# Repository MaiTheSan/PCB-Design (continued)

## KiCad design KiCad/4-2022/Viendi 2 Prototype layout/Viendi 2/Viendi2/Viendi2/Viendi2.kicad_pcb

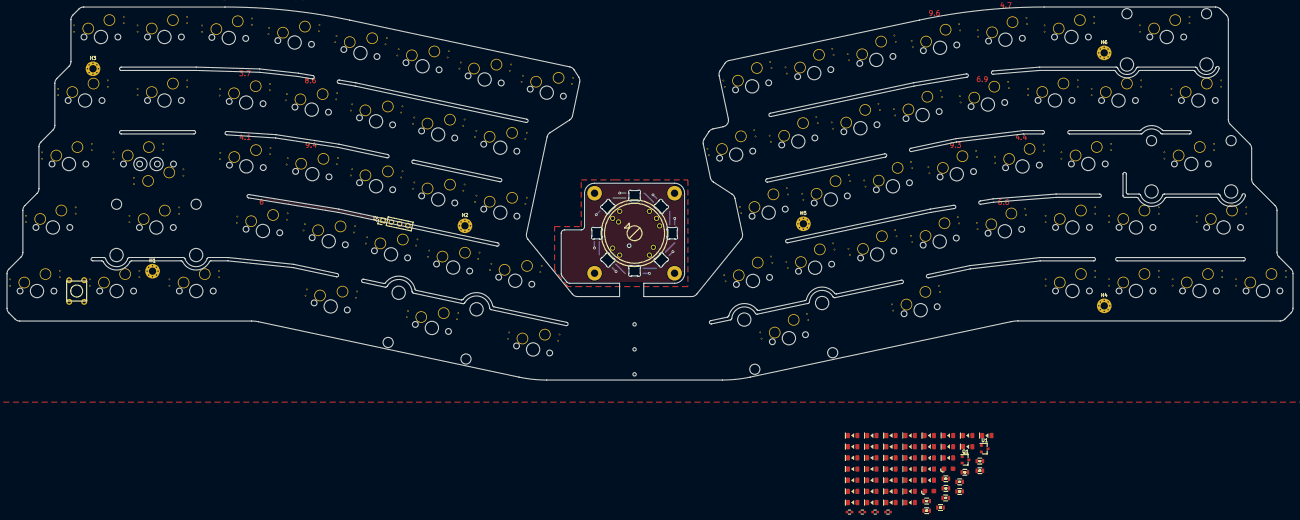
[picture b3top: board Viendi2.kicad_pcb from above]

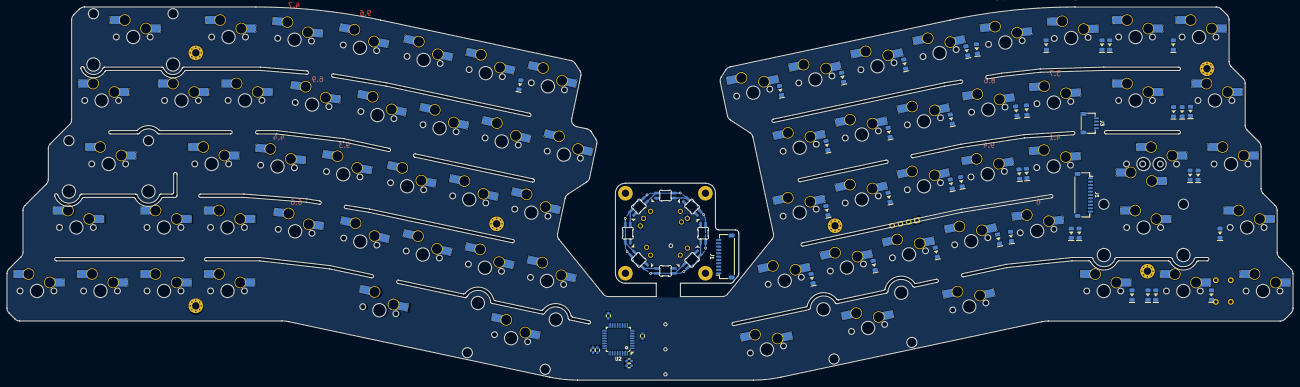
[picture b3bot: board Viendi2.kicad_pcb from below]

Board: 2 copper layers, 385.8 x 111.9 mm, 199 parts (48 on the bottom side), 116 nets.

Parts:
C1, C6: 4.7uF; C_0603
C2, C3, C4, C5, C11: 0.1uF; C_0603
C7, C8: 1uF; CP_EIA-3216
C9, C10: 1uF; C_0603
C12: 10uF (±5%); C_0603
D1, D2, D4, D6, D33, D34, D35, D36, D37, D38, D39, D40, D41, D42, D43, D44, D45, D46, D47, D48, D49, D50, D51, D52, D54, D55, D56, D57, D58, D59, D60, D61, D62, D63, D64, D65, D66, D67, D68, D69, D70, D71, D72, D74, D75, D76, D77, D78, D79, D80, D81, D82, D83, D84, D85, D86, D87, D88, D89, D90, D91, D92, D93, D94, D95, D96, D97, D98, D99, D100, D101, D102, D103, D104, D105, D106, D107: 1N4148W; DIODE_1206_SawnsProjects
H1, H2, H3, H4: MountingHole; MountingHole_2.2mm_M2_Pad
H1#2, H2#2, H3#2, H4#2, H5, H6: MountingHole; MountingHole_2.2mm_M2_Pad_Via
J1, J1#2: Conn_01x11_Female; JST_SH_SM11B-SRSS-TB_1x11-1MP_P1.00mm_Horizontal
J2: Conn_01x04; PinHeader_1x04_P2.54mm_Vertical
J3: Conn_01x04_Female; JST-SR-4
MX1, MX2, MX3, MX4, MX5, MX6, MX7, MX8, MX9, MX10, MX11, MX12, MX13, MX14, MX17, MX19, MX20, MX21, MX22, MX23, MX24, MX25, MX26, MX27, MX28, MX29, MX30, MX33, MX35, MX36, MX37, MX38, MX39, MX40, MX41, MX42, MX43, MX44, MX45, MX49, MX51, MX52, MX53, MX54, MX55, MX56, MX57, MX58, MX59, MX60, MX61, MX62, MX65, MX67, MX68, MX70, MX73, MX74, MX75, MX76: 1U; MXOnly-1U-Hotswap-Sawns
MX15: 2U; MXOnly-2U-Hotswap-Sawns
MX18, MX31, MX66, MX72: 1.5U; MXOnly-1.5U-Hotswap-Sawns
MX34: 1.75U; MXOnly-1.75U-Hotswap-Sawns
MX46, MX50: 2.25U; MXOnly-2.25U-Hotswap-Sawns
MX64: 2.25U; MXOnly-2.25U-Hotswap-ReversedStabilizers-Sawns
MX71: 2.75U; MXOnly-2.75U-Hotswap-ReversedStabilizers-Sawns
MX78: 1.25U; MXOnly-1.25U-Hotswap-Sawns
MX79: 1U; MXOnly-1.75U-Hotswap-Sawns
Q1: DTC123JKAT146; SOT-23
R1: 330R; R_0805
R2, R3: 22R; R_0805
R4: 1.5k; R_0805
R5, R6: 100k; R_0805
R7, R8: 10k; R_0805
R9: 100R; R_0805
R10: 330k (±1%); R_0805
R11: 1M (±1%); R_0805
RGB1, RGB2, RGB3, RGB4, RGB5, RGB6, RGB7, RGB8: WS2812B; MX_SK6812MINI-E_MID_Viendi2
SW1: StickSW+KNOB; RKJXT1F_4DirectionStickSW_RotaryEncoder
SW1#2: SW_Push; PushButton_6x6mm_TH_Pretty
U1: MCP1700-5002E_SOT23; SOT-23
U2: STM32F072CBTx; LQFP-48_7x7mm_P0.5mm

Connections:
+3V3: C1.1, C2.1, C3.1, C4.1, C5.1, C6.1, C8.1, J2.4, R4.1, R6.1, R7.2, R8.1, SW1#2.1, U1.2, U2.1, U2.9, U2.24, U2.36, U2.48
+5V: C7.1, J1#2.1, R5.2, U1.3
ABC1: U2.4, U2.10
ABC2: U2.3, U2.11
ABC3: U2.2, U2.12
B: D35.1, D69.1, D71.1, D74.1, D76.1, D78.1, D80.1, D82.1, D84.1, D86.1, D88.1, D90.1, D92.1, D94.1, D96.1
Boot0: C12.1, R10.1, R11.1
C: D33.1, D38.1, D39.1, D40.1, D41.1, D42.1, D43.1, D44.1, D45.1, D46.1, D47.1, D48.1, D49.1, D50.1, D51.1, D52.1, U2.16
Col0: MX1.1, MX17.1, MX33.1, MX49.1, MX65.1, U2.13
Col1: MX2.1, MX18.1, MX34.2, MX50.1, MX66.1, MX78.1, U2.14
Col3: MX3.1, MX19.1, MX35.1, MX51.1, U2.22
Col4: MX4.1, MX20.1, MX36.1, MX52.1, MX68.1, U2.21
Col5: MX5.1, MX21.1, MX37.1, MX53.1, MX64.1, U2.20
Col6: MX6.1, MX22.1, MX38.1, MX54.1, U2.19
Col7: MX7.1, MX23.1, MX39.1, MX55.1, MX70.1, U2.18
Col8: MX8.1, U2.17
Col9: MX9.1, MX24.1, MX40.1, MX56.1, MX71.1, U2.39
Col10: MX10.1, MX25.1, MX41.1, MX57.1, MX72.1, U2.46
Col11: MX11.1, MX26.1, MX42.1, MX58.1, MX73.1, U2.45
Col12: MX12.1, MX27.1, MX43.1, MX59.1, MX74.1, U2.38
Col13: MX13.1, MX28.1, MX44.1, MX60.1, MX75.1, U2.43
Col14: MX14.1, MX29.1, MX45.1, MX61.1, MX76.1, U2.42
Col15: MX15.1, MX30.1, MX46.1, MX62.1, U2.41
Col16: MX31.1, MX79.1, U2.40
Com: D34.1, D54.1, D55.1, D56.1, D57.1, D58.1, D59.1, D60.1, D61.1, D62.1, D63.1, D64.1, D65.1, D66.1, D67.1, D68.1, U2.15
D: D37.1, D70.1, D72.1, D75.1, D77.1, D79.1, D81.1, D83.1, D85.1, D87.1, D89.1, D91.1, D93.1, D95.1, D97.1, D98.1
E_A: C10.1, J1#2.10, R8.2, U2.30
E_B: C9.2, J1#2.4, R7.1, U2.28
GND: C1.2, C2.2, C3.2, C4.2, C5.2, C6.2, C7.2, C8.2, C9.1, C10.2, C11.1, C12.2, J1#2.11, J2.1, Q1.2, R5.1, R6.2, R11.2, U1.1, U2.8, U2.23, U2.35, U2.47
NRST: C11.2, R9.1, U2.7
unnamed: D1.1, R10.2
unnamed: D1.2, Q1.1, SW1#2.2
unnamed: D2.2, MX65.2
unnamed: D4.2, MX66.2
unnamed: D6.2, MX67.2
unnamed: D33.2, J1#2.2
unnamed: D34.2, J1#2.3
unnamed: D35.2, J1#2.5
unnamed: D36.2, J1#2.8
unnamed: D37.2, J1#2.9
unnamed: D38.2, MX1.2
unnamed: D39.2, MX2.2
unnamed: D40.2, MX3.2
unnamed: D41.2, MX4.2
unnamed: D42.2, MX5.2
unnamed: D43.2, MX6.2
unnamed: D44.2, MX7.2
unnamed: D45.2, MX8.2
unnamed: D46.2, MX9.2
unnamed: D47.2, MX10.2
unnamed: D48.2, MX11.2
unnamed: D49.2, MX12.2
unnamed: D50.2, MX13.2
unnamed: D51.2, MX14.2
unnamed: D52.2, MX15.2
unnamed: D54.2, MX17.2
unnamed: D55.2, MX18.2
unnamed: D56.2, MX19.2
unnamed: D57.2, MX20.2
unnamed: D58.2, MX21.2
unnamed: D59.2, MX22.2
unnamed: D60.2, MX23.2
unnamed: D61.2, MX24.2
unnamed: D62.2, MX25.2
unnamed: D63.2, MX26.2
unnamed: D64.2, MX27.2
unnamed: D65.2, MX28.2
unnamed: D66.2, MX29.2
unnamed: D67.2, MX30.2
unnamed: D68.2, MX31.2
unnamed: D69.2, MX33.2
unnamed: D70.2, MX49.2
unnamed: D71.2, MX34.1, MX78.2
unnamed: D72.2, MX50.2
unnamed: D74.2, MX35.2
unnamed: D75.2, MX51.2
unnamed: D76.2, MX36.2
unnamed: D77.2, MX52.2
unnamed: D78.2, MX37.2
unnamed: D79.2, MX53.2
unnamed: D80.2, MX38.2
unnamed: D81.2, MX54.2
unnamed: D82.2, MX39.2
unnamed: D83.2, MX55.2
unnamed: D84.2, MX40.2
unnamed: D85.2, MX56.2
unnamed: D86.2, MX41.2
unnamed: D87.2, MX57.2
unnamed: D88.2, MX42.2
unnamed: D89.2, MX58.2
unnamed: D90.2, MX43.2
unnamed: D91.2, MX59.2
unnamed: D92.2, MX44.2
unnamed: D93.2, MX60.2
unnamed: D94.2, MX45.2
unnamed: D95.2, MX61.2
unnamed: D96.2, MX46.2
unnamed: D97.2, MX62.2
unnamed: D98.2, MX79.2
unnamed: D99.2, MX68.2
unnamed: D100.2, MX64.2
unnamed: D101.2, MX70.2
unnamed: D102.2, MX71.2
unnamed: D103.2, MX72.2
unnamed: D104.2, MX73.2
unnamed: D105.2, MX74.2
unnamed: D106.2, MX75.2
unnamed: D107.2, MX76.2
unnamed: J1#2.6, R1.1
unnamed: Q1.3, R9.2
unnamed: R2.2, U2.32
unnamed: R3.2, R4.2, U2.33
Push: J1#2.7, U2.29
RGB_IN: R1.2, U2.31
SWCLK: J2.3, U2.37
SWDIO: J2.2, U2.34

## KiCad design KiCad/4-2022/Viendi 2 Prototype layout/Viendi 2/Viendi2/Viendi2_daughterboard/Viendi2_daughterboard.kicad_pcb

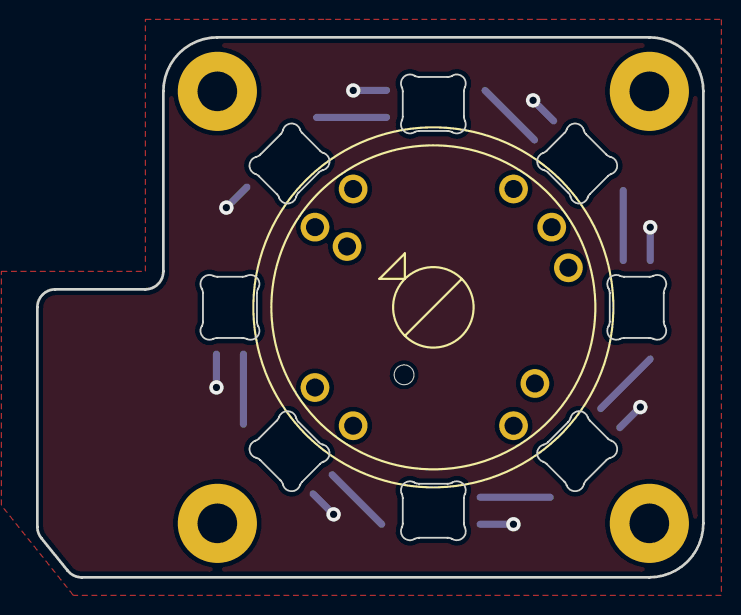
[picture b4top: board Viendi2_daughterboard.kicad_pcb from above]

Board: 2 copper layers, 37.0 x 30.0 mm, 14 parts (1 on the bottom side), 9 nets.

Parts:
H1, H2, H3, H4: MountingHole; MountingHole_2.2mm_M2_Pad
J1: Conn_01x11_Female; JST_SH_SM11B-SRSS-TB_1x11-1MP_P1.00mm_Horizontal
RGB1, RGB2, RGB3, RGB4, RGB5, RGB6, RGB7, RGB8: WS2812B; MX_SK6812MINI-E_MID_Viendi2
SW1: StickSW+KNOB; RKJXT1F_4DirectionStickSW_RotaryEncoder

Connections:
+5V: RGB1.1, RGB2.1, RGB3.1, RGB4.1, RGB5.1, RGB6.1, RGB7.1, RGB8.1
GND: RGB1.3, RGB2.3, RGB3.3, RGB4.3, RGB5.3, RGB6.3, RGB7.3, RGB8.3, SW1.7, SW1.10
unnamed: RGB1.2, RGB2.4
unnamed: RGB2.2, RGB3.4
unnamed: RGB3.2, RGB4.4
unnamed: RGB4.2, RGB5.4
unnamed: RGB5.2, RGB6.4
unnamed: RGB6.2, RGB7.4
unnamed: RGB7.2, RGB8.4

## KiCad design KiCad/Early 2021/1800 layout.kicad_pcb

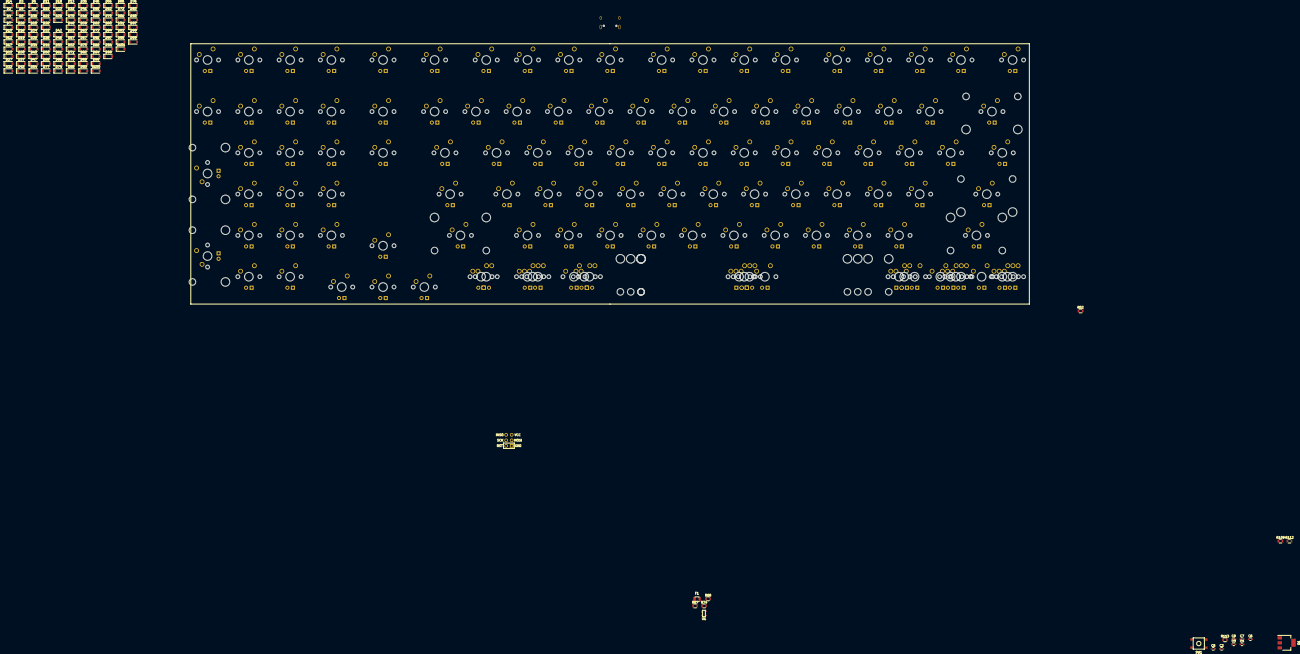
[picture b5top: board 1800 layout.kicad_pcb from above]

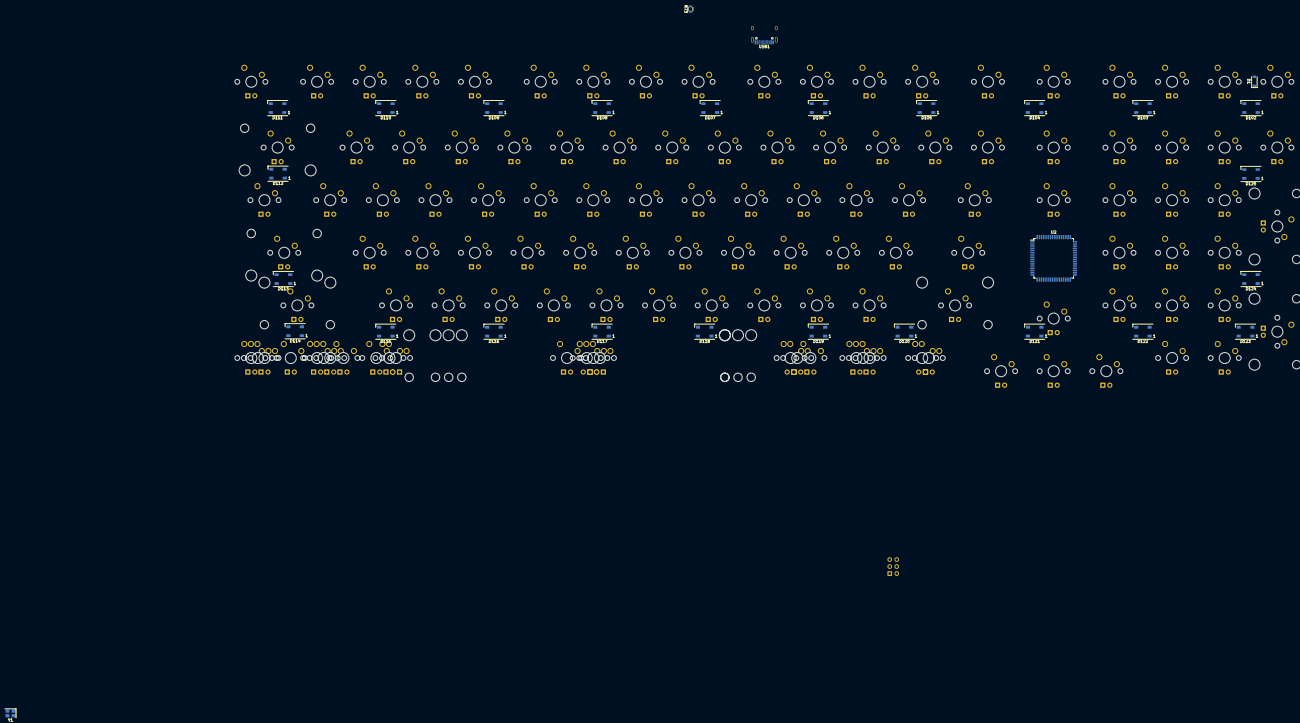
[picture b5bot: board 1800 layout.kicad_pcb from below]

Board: 2 copper layers, 266 parts (29 on the bottom side), 143 nets, no tracks yet.

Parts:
C2, C5: 1uF; C_0603
C3, C4: 22pF; C_0603
C6, C7, C8: 0.1uF; C_0603
D1, D2, D3, D4, D5, D6, D7, D8, D9, D10, D11, D12, D13, D14, D15, D16, D17, D18, D19, D20, D21, D22, D23, D24, D25, D26, D27, D28, D29, D30, D31, D32, D33, D34, D35, D36, D37, D38, D39, D40, D41, D42, D43, D44, D45, D46, D47, D48, D49, D50, D51, D52, D53, D54, D55, D56, D57, D58, D59, D60, D61, D62, D63, D64, D65, D66, D67, D68, D69, D70, D71, D72, D73, D74, D75, D76, D77, D78, D79, D80, D81, D82, D83, D84, D85, D86, D87, D88, D89, D90, D91, D92, D93, D94, D95, D96, D97, D98, D99, D100, D101: SOD_123; D_SOD-123-Pretty
D102, D103, D104, D105, D106, D107, D108, D109, D110, D111, D112, D113, D114, D115, D116, D117, D118, D119, D120, D121, D122, D123, D124, D125: WS2812B; LED_WS2812B_PLCC4_5.0x5.0mm_P3.2mm
F1: 500mA; Fuse_SMD1206_Reflow
J1: AVR-ISP-6; Reset_Pretty-Mask
MX_0, MX_1, MX_2, MX_3, MX_4, MX_5, MX_6, MX_7, MX_8, MX_9: 1U; MXOnly-1U
MX_'1: 1U; MXOnly-1U
MX_+1: 1U; MXOnly-1U
MX_-1: 1U; MXOnly-1U
MX_/?/2: 1U; MXOnly-1U
MX_;1: 1U; MXOnly-1U
MX_<2: 1U; MXOnly-1U
MX_>2: 1U; MXOnly-1U
MX_A1: 1U; MXOnly-1U
MX_ALT1: 1,5U FLIPPED; MXOnly-1.5U-FLIPPED
MX_ALT2, MX_ALT3: 1,25U; MXOnly-1.25U
MX_BkSp1: 2U; MXOnly-2U
MX_CapLk1: 1,75U; MXOnly-1.75U
MX_D1: 1U; MXOnly-1U
MX_Delete1: 1U; MXOnly-1U
MX_Down1: 1U; MXOnly-1U
MX_E1: 1U; MXOnly-1U
MX_ENTER1: 2,25U; MXOnly-2.25U
MX_ESC1: 1U; MXOnly-1U
MX_F1, MX_F2, MX_F3, MX_F4, MX_F5, MX_F6, MX_F7, MX_F8, MX_F9, MX_F10, MX_F11, MX_F12, MX_F13, MX_F14: 1U; MXOnly-1U
MX_FN1, MX_FN2, MX_FN3, MX_FN4: 1U; MXOnly-1U
MX_G1: 1U; MXOnly-1U
MX_H1: 1U; MXOnly-1U
MX_I1: 1U; MXOnly-1U
MX_J1: 1U; MXOnly-1U
MX_K1: 1U; MXOnly-1U
MX_L1: 1U; MXOnly-1U
MX_LControl1: 1,5U; MXOnly-1.5U-FLIPPED
MX_LControl2: 1,25; MXOnly-1.25U
MX_LShift1: 2,25U FLIPPED; MXOnly-2.25U-ReversedStabilizers
MX_LWin1, MX_LWin3: 1U; MXOnly-1U
MX_LWin2: 1,25U NoLed; MXOnly-1.25U-NoLED
MX_Left1: 1U; MXOnly-1U
MX_O1: 1U; MXOnly-1U
MX_P1: 1U; MXOnly-1U
MX_PrtSc1: 1U; MXOnly-1U
MX_Q1: 1U; MXOnly-1U
MX_R1: 1U; MXOnly-1U
MX_RAlt1, MX_RAlt3: 1,25U; MXOnly-1.25U
MX_RAlt2: 1,5U FLIPPED; MXOnly-1.5U-FLIPPED
MX_RAlt4: 1,5U; MXOnly-1.5U
MX_RControl1: 1,25U NoLed; MXOnly-1.25U-NoLED
MX_RControl2: 1U; MXOnly-1U
MX_RControl3: 1,5U; MXOnly-1.5U
MX_RShift2: 2,75U FLIPPED; MXOnly-2.75U-ReversedStabilizers
MX_RWin1: NoLed; MXOnly-1.25U-NoLED
MX_RWin2: 1,5U; MXOnly-1.5U
MX_RWin3, MX_RWin4: 1U; MXOnly-1U
MX_Right1: 1U; MXOnly-1U
MX_S1: 1U; MXOnly-1U
MX_SpaceBar1, MX_SpaceBar2: 6,25U FLIPPED; MXOnly-6.25U-FLIPPED-ReversedStabilizers
MX_SpaceBar3, MX_SpaceBar4: 7U; MXOnly-7U-ReversedStabilizers
MX_T1: 1U; MXOnly-1U
MX_U1: 1U; MXOnly-1U
MX_W1: 1U; MXOnly-1U
MX_Y1: 1U; MXOnly-1U
MX_[1: 1U; MXOnly-1U
MX_]1: 1U; MXOnly-1U
MX_`~1: 1U; MXOnly-1U
MX_b1: 1U; MXOnly-1U
MX_c1: 1U; MXOnly-1U
MX_insert1: 1U; MXOnly-1U
MX_m2: 1U; MXOnly-1U
MX_n2: 1U; MXOnly-1U
MX_num0, MX_num1, MX_num2, MX_num3, MX_num4, MX_num5, MX_num6, MX_num7, MX_num8, MX_num9: 1U; MXOnly-1U
MX_num*1: 1U; MXOnly-1U
MX_num+1: 2U; MXOnly-2U
MX_num-1: 1U; MXOnly-1U
MX_num/1: 1U; MXOnly-1U
MX_numDel1: 1U; MXOnly-1U
MX_numEnter1: 2U; MXOnly-2U
MX_numLk1: 1U; MXOnly-1U
MX_tab1: 1,5U; MXOnly-1.5U
MX_up1: 1U; MXOnly-1U
MX_v1: 1U; MXOnly-1U
MX_x1: 1U; MXOnly-1U
MX_z1: 1U; MXOnly-1U
MX_|\1: 1.5U; MXOnly-1.5U
Q1: DSS60601MZ4-13; SOT-223-3_TabPin2
R52: 500; R_0805
R67, R68: 22; R_0805
R73, R74: 5.1k; R_0805
R109: 1.5k; R_0805
R112: 10k; R_0805
R113: 1k; R_0805
SW1: SW_Push; SKQG-1155865
U1: PRTR5V0U2X; SOT143B
U2: AT90USB1286-AU; TQFP-64_14x14mm_P0.8mm
USB1: HRO-TYPE-C-31-M-12; HRO-TYPE-C-31-M-12-Assembly
Y1: 16MHz; Crystal_SMD_3225-4Pin_3.2x2.5mm

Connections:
+5V: C5.2, C6.2, C7.2, C8.2, F1.1, J1.2, R112.1, U2.3, U2.8, U2.21, U2.52, U2.64
D+: R68.1, U2.5
D-: R67.1, U2.4
GND: C2.2, C3.2, C4.2, C5.1, C6.1, C7.1, C8.1, J1.6, Q1.3, R73.1, R74.1, R113.2, SW1.1, U1.1, U2.6, U2.22, U2.53, U2.63, USB1.1, USB1.12, USB1.13, Y1.2, Y1.4
MISO: J1.1, U2.13
MOSI: J1.4, U2.12
unnamed: C2.1, U2.7
unnamed: D1.2, MX_FN1.2
unnamed: D2.2, MX_num-1.2
unnamed: D3.2, MX_num+1.2
unnamed: D4.2, MX_numEnter1.2
unnamed: D5.2, MX_FN2.2
unnamed: D6.2, MX_num*1.2
unnamed: D7.2, MX_num7.2
unnamed: D8.2, MX_num4.2
unnamed: D9.2, MX_num1.2
unnamed: D10.2, MX_num0.2
unnamed: D11.2, MX_FN3.2
unnamed: D12.2, MX_num/1.2
unnamed: D13.2, MX_num8.2
unnamed: D14.2, MX_num5.2
unnamed: D15.2, MX_num2.2
unnamed: D16.2, MX_numDel1.2
unnamed: D17.2, MX_FN4.2
unnamed: D18.2, MX_numLk1.2
unnamed: D19.2, MX_num9.2
unnamed: D20.2, MX_num6.2
unnamed: D21.2, MX_num3.2
unnamed: D22.2, MX_Right1.2
unnamed: D23.2, MX_PrtSc1.2
unnamed: D24.2, MX_insert1.2
unnamed: D25.2, MX_Delete1.2
unnamed: D26.2, MX_up1.2
unnamed: D27.2, MX_Down1.2
unnamed: D28.2, MX_ESC1.2
unnamed: D29.2, MX_`~1.2
unnamed: D30.2, MX_tab1.2
unnamed: D31.2, MX_CapLk1.2
unnamed: D32.2, MX_LShift1.2
unnamed: D33.2, MX_Left1.2
unnamed: D34.2, MX_F1.2
unnamed: D35.2, MX_1.2
unnamed: D36.2, MX_Q1.2
unnamed: D37.2, MX_A1.2
unnamed: D38.2, MX_z1.2
unnamed: D39.2, MX_LControl1.2
unnamed: D40.2, MX_F2.2
unnamed: D41.2, MX_2.2
unnamed: D42.2, MX_W1.2
unnamed: D43.2, MX_S1.2
unnamed: D44.2, MX_x1.2
unnamed: D45.2, MX_LWin1.2
unnamed: D46.2, MX_F3.2
unnamed: D47.2, MX_3.2
unnamed: D48.2, MX_E1.2
unnamed: D49.2, MX_D1.2
unnamed: D50.2, MX_c1.2
unnamed: D51.2, MX_ALT1.2
unnamed: D52.2, MX_F4.2
unnamed: D53.2, MX_4.2
unnamed: D54.2, MX_R1.2
unnamed: D55.2, MX_F5.2
unnamed: D56.2, MX_v1.2
unnamed: D57.2, MX_5.2
unnamed: D58.2, MX_T1.2
unnamed: D59.2, MX_G1.2
unnamed: D60.2, MX_b1.2
unnamed: D61.2, MX_SpaceBar1.2
unnamed: D62.2, MX_F6.2
unnamed: D63.2, MX_6.2
unnamed: D64.2, MX_Y1.2
unnamed: D65.2, MX_H1.2
unnamed: D66.2, MX_n2.2
unnamed: D67.2, MX_F7.2
unnamed: D68.2, MX_7.2
unnamed: D69.2, MX_U1.2
unnamed: D70.2, MX_J1.2
unnamed: D71.2, MX_m2.2
unnamed: D72.2, MX_F8.2
unnamed: D73.2, MX_8.2
unnamed: D74.2, MX_I1.2
unnamed: D75.2, MX_K1.2
unnamed: D76.2, MX_<2.2
unnamed: D77.2, MX_RAlt1.2
unnamed: D78.2, MX_F9.2
unnamed: D79.2, MX_9.2
unnamed: D80.2, MX_O1.2
unnamed: D81.2, MX_L1.2
unnamed: D82.2, MX_>2.2
unnamed: D83.2, MX_RWin1.2
unnamed: D84.2, MX_F10.2
unnamed: D85.2, MX_0.2
unnamed: D86.2, MX_P1.2
unnamed: D87.2, MX_;1.2
unnamed: D88.2, MX_/?/2.2
unnamed: D89.2, MX_RControl1.2
unnamed: D90.2, MX_F11.2
unnamed: D91.2, MX_-1.2
unnamed: D92.2, MX_[1.2
unnamed: D93.2, MX_'1.2
unnamed: D94.2, MX_F12.2
unnamed: D95.2, MX_+1.2
unnamed: D96.2, MX_]1.2
unnamed: D97.2, MX_F13.2
unnamed: D98.2, MX_F14.2
unnamed: D99.2, MX_BkSp1.2
unnamed: D100.2, MX_ENTER1.2
unnamed: D101.2, MX_RShift2.2
unnamed: D102.1, D103.1, D104.1, D105.1, D106.1, D107.1, D108.1, D109.1, D110.1, D111.1, D112.1, D113.1, D114.1, D115.1, D116.1, D117.1, D118.1, D119.1, D120.1, D121.1, D122.1, D123.1, D124.1, D125.1
unnamed: D102.2, D103.4
unnamed: D102.3, D103.3, D104.3, D105.3, D106.3, D107.3, D108.3, D109.3, D110.3, D111.3, D112.3, D113.3, D114.3, D115.3, D116.3, D117.3, D118.3, D119.3, D120.3, D121.3, D122.3, D123.3, D124.3, D125.3
unnamed: D103.2, D104.4
unnamed: D104.2, D105.4
unnamed: D105.2, D106.4
unnamed: D106.2, D107.4
unnamed: D107.2, D108.4
unnamed: D108.2, D109.4
unnamed: D109.2, D110.4
unnamed: D110.2, D111.4
unnamed: D111.2, D112.4
unnamed: D112.2, D113.4
unnamed: D113.2, D114.4
unnamed: D114.2, D115.4
unnamed: D116.4, D117.2
unnamed: D117.4, D118.2
unnamed: D118.4, D119.2
unnamed: D119.4, D120.2
unnamed: D120.4, D121.2
unnamed: D121.4, D122.2
unnamed: D122.4, D123.2
unnamed: D123.4, D124.2
unnamed: D124.4, D125.2
unnamed: Q1.1, R109.1
unnamed: R67.2, U1.3, USB1.5, USB1.7
unnamed: R68.2, U1.2, USB1.6, USB1.8
unnamed: R73.2, USB1.4
unnamed: R74.2, USB1.10
unnamed: R113.1, U2.43
RESET: J1.5, R112.2, SW1.2, U2.20
SCK: J1.3, U2.11
VCC: F1.2, U1.4, USB1.2, USB1.11
XTAL1: C3.1, U2.24, Y1.1
XTAL2: C4.1, U2.23, Y1.3

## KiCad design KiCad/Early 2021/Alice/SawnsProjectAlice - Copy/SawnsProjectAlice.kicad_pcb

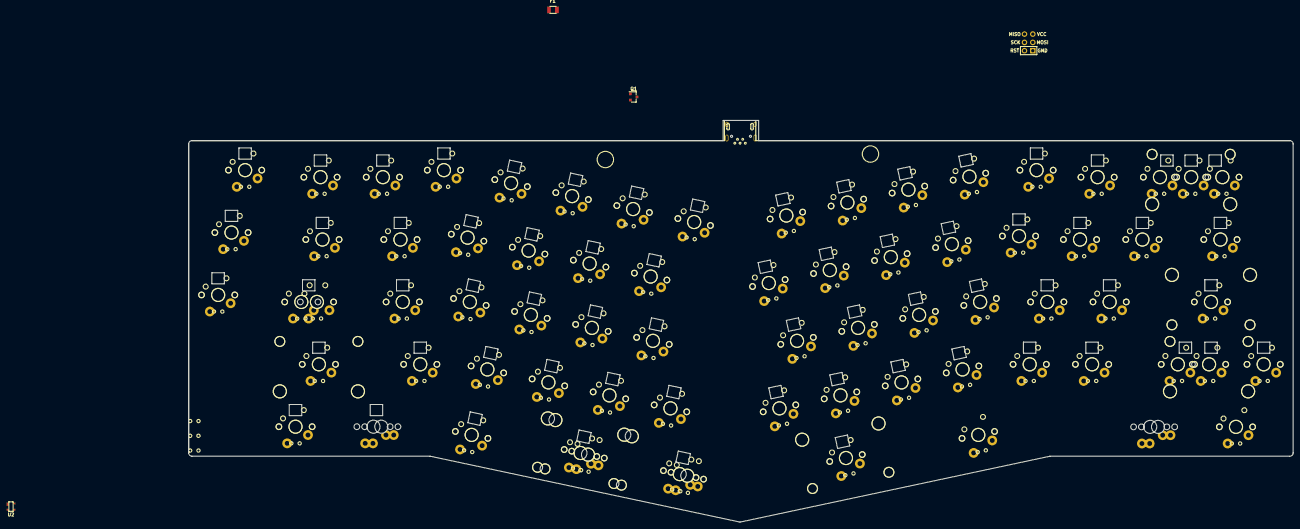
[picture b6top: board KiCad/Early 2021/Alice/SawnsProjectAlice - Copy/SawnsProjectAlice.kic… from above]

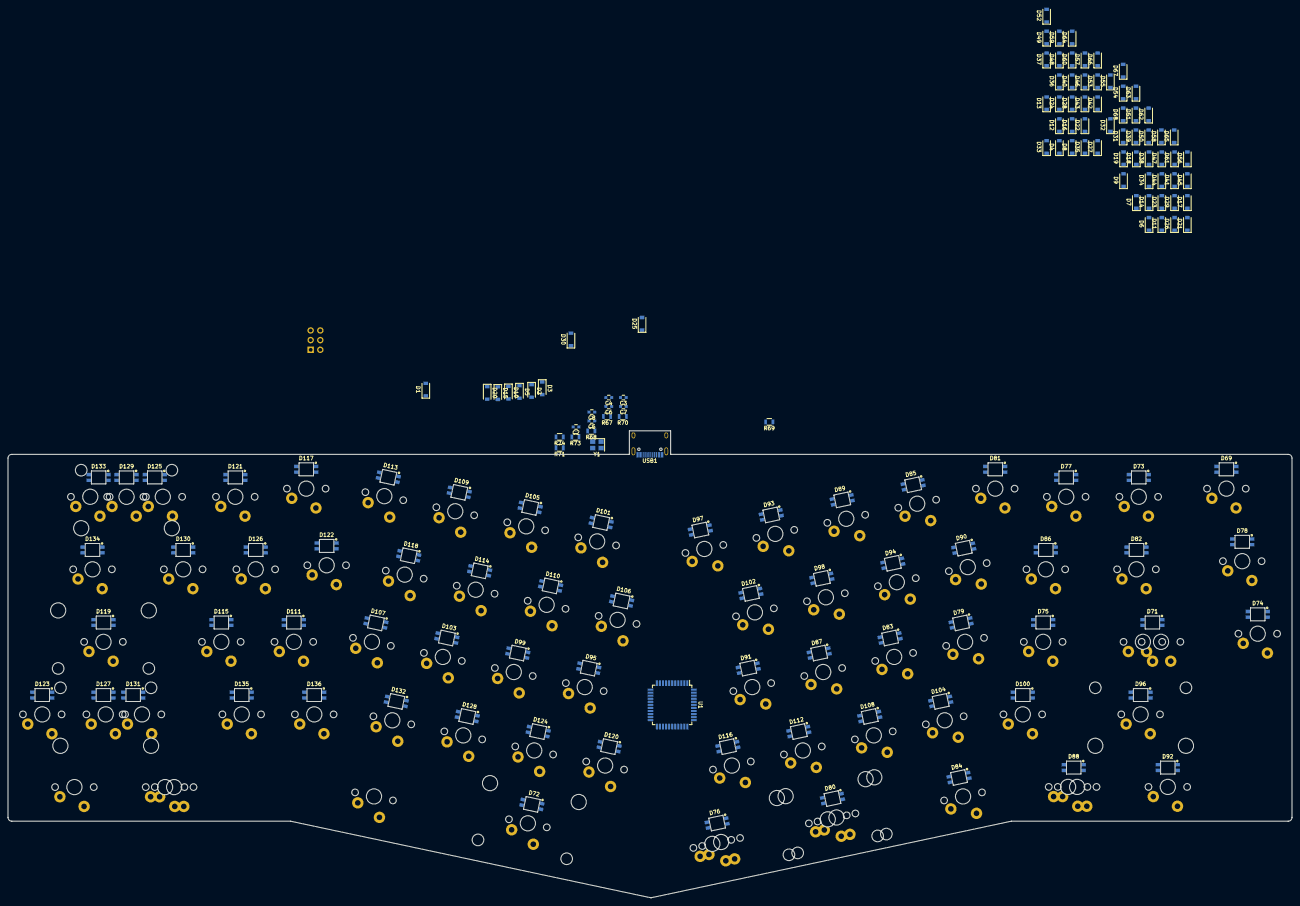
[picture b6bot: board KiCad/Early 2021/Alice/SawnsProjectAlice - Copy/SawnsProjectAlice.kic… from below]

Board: 2 copper layers, 337.2 x 122.6 mm, 231 parts (152 on the bottom side), 171 nets, no tracks yet.

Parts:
C2: 10uF; C_0603
C3, C4, C5: 0.1uF; C_0603
C6: 1uF; C_0603
C7, C8: 22pF; C_0603
D1, D2, D3, D4, D5, D6, D7, D8, D9, D10, D11, D12, D13, D14, D15, D16, D17, D18, D19, D20, D21, D22, D23, D24, D25, D26, D27, D28, D29, D30, D31, D32, D33, D34, D35, D36, D37, D38, D39, D40, D41, D42, D43, D44, D45, D46, D47, D48, D49, D50, D51, D52, D53, D54, D55, D56, D57, D58, D59, D60, D61, D62, D63, D64, D65, D66, D67, D68: SOD_123; D_SOD-123-Pretty
D69, D71, D72, D73, D74, D75, D76, D77, D78, D79, D80, D81, D82, D83, D84, D85, D86, D87, D88, D89, D90, D91, D92, D93, D94, D95, D96, D97, D98, D99, D100, D101, D102, D103, D104, D105, D106, D107, D108, D109, D110, D111, D112, D113, D114, D115, D116, D117, D118, D119, D120, D121, D122, D123, D124, D125, D126, D127, D128, D129, D130, D131, D132, D133, D134, D135, D136: WS2812B; RGB-6028
F1: 500mA; Fuse_SMD1206_Reflow
K_0, K_1, K_2, K_3, K_4, K_5, K_6, K_7, K_8, K_9, K_.1: 1U; MXOnly-1U-NoLED
K_'1: 1U; MXOnly-1U-NoLED
K_+1: 1U; MXOnly-1U-NoLED
K_,1: 1U; MXOnly-1U-NoLED
K_-_1: 1U; MXOnly-1U-NoLED
K_/?/1: 1U; MXOnly-1U-NoLED
K_;1: 1U; MXOnly-1U-NoLED
K_A1: 1U; MXOnly-1U-NoLED
K_Alt1: 1.25U; MXOnly-1.25U-NoLED
K_B1: 1U; MXOnly-1U-NoLED
K_BkSp1: 1U; MXOnly-1U-NoLED
K_BkSp2: 2U; MXOnly-2U-ReversedStabilizers-NoLED
K_C1: 1U; MXOnly-1U-NoLED
K_CapLk1, K_CapLk2: MX-1U-MX_Alps_Hybrids; MXOnly-1U-NoLED
K_D1: 1U; MXOnly-1U-NoLED
K_Delete1: 1U; MXOnly-1U-NoLED
K_E1: 1U; MXOnly-1U-NoLED
K_ESC1: 1U; MXOnly-1U-NoLED
K_Enter1: 2.25U; MXOnly-2.25U-NoLED
K_F1: 1U; MXOnly-1U-NoLED
K_FN1: 1U; MXOnly-1U-NoLED
K_G1: 1U; MXOnly-1U-NoLED
K_H1: 1U; MXOnly-1U-NoLED
K_I1: 1U; MXOnly-1U-NoLED
K_J1: 1U; MXOnly-1U-NoLED
K_K1: 1U; MXOnly-1U-NoLED
K_L1: 1U; MXOnly-1U-NoLED
K_LControl1: 1.5U; MXOnly-1.5U-NoLED
K_LShift1: MX-1U-MX_Alps_Hybrids; MXOnly-2.25U-ReversedStabilizers-NoLED
K_LWin1: 1.25U; MXOnly-1.25U-NoLED
K_LWin2: 1U; MXOnly-1U-NoLED
K_M1: 1U; MXOnly-1U-NoLED
K_N1: 1U; MXOnly-1U-NoLED
K_O1: 1U; MXOnly-1U-NoLED
K_P1: 1U; MXOnly-1U-NoLED
K_PgDn1: 1U; MXOnly-1U-NoLED
K_PgUp1: 1U; MXOnly-1U-NoLED
K_Q1: 1U; MXOnly-1U-NoLED
K_R1: 1U; MXOnly-1U-NoLED
K_RShift1: 1.75U; MXOnly-1.75U-NoLED
K_RShift2: 2.75U; MXOnly-2.75U-ReversedStabilizers-NoLED
K_RWin1: 1U; MXOnly-1U-NoLED
K_RWin2: 1.25U; MXOnly-1.25U-NoLED
K_S1: 1U; MXOnly-1U-NoLED
K_T1: 1U; MXOnly-1U-NoLED
K_Tab1: 1.5U; MXOnly-1.5U-NoLED
K_U1: 1U; MXOnly-1U-NoLED
K_V1: 1U; MXOnly-1U-NoLED
K_W1: 1U; MXOnly-1U-NoLED
K_X1: 1U; MXOnly-1U-NoLED
K_Y1: 1U; MXOnly-1U-NoLED
K_Z1: 1U; MXOnly-1U-NoLED
K_]}1: 1U; MXOnly-1U-NoLED
K_`1: 1U; MXOnly-1U-NoLED
K_xn1: 1U; MXOnly-1U-NoLED
K_{[1: 1U; MXOnly-1U-NoLED
K_|\1: 1.5U; MXOnly-1.5U-NoLED
MX1, MX1_1: 2U; MXOnly-2U-NoLED
MX2, MX2_1, MX4: MX-1U-MX_Alps_Hybrids; MXOnly-1U-NoLED
MX3: 2.75U; MXOnly-2.75U-NoLED
MX5: 1.5U; MXOnly-1.5U-NoLED
Q1: 2N7002; SOT-23
R67, R68: 22; R_0805
R69, R71: 1k; R_0805
R70: 10k; R_0805
R73, R74: 5.1k; R_0805
U1: ATmega32U4-AU; TQFP-44_10x10mm_P0.8mm
U2: PRTR5V0U2X; SOT143B
U3: STF202-22T1G; Reset_Pretty
USB1: HRO-TYPE-C-31-M-12; HRO-TYPE-C-31-M-12-Assembly
Y1: 16Mhz; Crystal_SMD_3225-4Pin_3.2x2.5mm

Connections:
+5V: C2.2, C3.2, C4.2, C5.2, D69.1, D71.1, D72.1, D73.1, D74.1, D75.1, D76.1, D77.1, D78.1, D79.1, D80.1, D81.1, D82.1, D83.1, D84.1, D85.1, D86.1, D87.1, D88.1, D89.1, D90.1, D91.1, D92.1, D93.1, D94.1, D95.1, D96.1, D97.1, D98.1, D99.1, D100.1, D101.1, D102.1, D103.1, D104.1, D105.1, D106.1, D107.1, D108.1, D109.1, D110.1, D111.1, D112.1, D113.1, D114.1, D115.1, D116.1, D117.1, D118.1, D119.1, D120.1, D121.1, D122.1, D123.1, D124.1, D125.1, D126.1, D127.1, D128.1, D129.1, D130.1, D131.1, D132.1, D133.1, D134.1, D135.1, D136.1, F1.1, R70.1, U1.2, U1.7, U1.14, U1.24, U1.34, U1.44, U3.2
/MOSI: U1.10, U3.4
/SCK: U1.9, U3.3
Col0: K_CapLk1.1, K_CapLk2.2, K_LControl1.1, K_LShift1.1, K_Tab1.1, K_`1.1
Col1: K_1.1, K_A1.1, K_LWin1.1, K_LWin2.1, K_Q1.1, K_Z1.1
Col2: K_2.1, K_Alt1.1, K_S1.1, K_W1.1, K_X1.1
Col5: K_5.1, K_F1.1, K_R1.1, K_V1.1, MX2.1, MX2_1.1
Col6: K_6.1, K_B1.1, K_G1.1, K_T1.1
Col7: K_7.1, K_H1.1, K_Y1.1, K_xn1.1, U1.11, U3.1
Col8: K_8.1, K_J1.1, K_N1.1, K_U1.1, MX3.1
Col9: K_9.1, K_I1.1, K_K1.1, K_M1.1
Col10: K_0.1, K_,1.1, K_L1.1, K_O1.1, MX4.1
Col11: K_-_1.1, K_.1.1, K_;1.1, K_P1.1
Col12: K_'1.1, K_+1.1, K_/?/1.1, K_{[1.1
Col13: K_BkSp1.1, K_BkSp2.1, K_RShift1.1, K_RShift2.1, K_RWin1.1, K_RWin2.1, K_]}1.1
Col14: K_Delete1.1, K_Enter1.1, K_FN1.1, K_|\1.1, MX5.1
Col-1: K_ESC1.1, K_PgDn1.1, K_PgUp1.1
D+: R68.1, U1.4
D-: R67.1, U1.3
GND: C2.1, C3.1, C4.1, C5.1, C6.2, C7.2, C8.2, D69.3, D71.3, D72.3, D73.3, D74.3, D75.3, D76.3, D77.3, D78.3, D79.3, D80.3, D81.3, D82.3, D83.3, D84.3, D85.3, D86.3, D87.3, D88.3, D89.3, D90.3, D91.3, D92.3, D93.3, D94.3, D95.3, D96.3, D97.3, D98.3, D99.3, D100.3, D101.3, D102.3, D103.3, D104.3, D105.3, D106.3, D107.3, D108.3, D109.3, D110.3, D111.3, D112.3, D113.3, D114.3, D115.3, D116.3, D117.3, D118.3, D119.3, D120.3, D121.3, D122.3, D123.3, D124.3, D125.3, D126.3, D127.3, D128.3, D129.3, D130.3, D131.3, D132.3, D133.3, D134.3, D135.3, D136.3, Q1.2, R71.1, R73.1, R74.1, U1.5, U1.15, U1.23, U1.35, U1.43, U2.1, U3.6, USB1.1, USB1.12, USB1.13, Y1.2, Y1.4
unnamed: C6.1, U1.6
unnamed: C7.1, U1.17, Y1.1
unnamed: C8.1, U1.16, Y1.3
unnamed: D1.2, K_PgUp1.2
unnamed: D2.2, K_`1.2
unnamed: D3.2, K_ESC1.2
unnamed: D4.2, K_PgDn1.2
unnamed: D5.2, K_1.2
unnamed: D6.2, K_Tab1.2
unnamed: D7.2, K_CapLk1.2, K_CapLk2.1
unnamed: D8.2, K_LShift1.2
unnamed: D9.2, K_LControl1.2
unnamed: D10.2, K_2.2
unnamed: D11.2, K_Q1.2
unnamed: D12.2, K_A1.2
unnamed: D13.2, K_Z1.2
unnamed: D14.2, K_LWin1.2, K_LWin2.2
unnamed: D15.2, K_3.2
unnamed: D16.2, K_W1.2
unnamed: D17.2, K_S1.2
unnamed: D18.2, K_X1.2
unnamed: D19.2, K_Alt1.2
unnamed: D20.2, K_4.2
unnamed: D21.2, K_E1.2
unnamed: D22.2, K_D1.2
unnamed: D23.2, K_C1.2
unnamed: D24.2, MX1.2, MX1_1.2
unnamed: D25.2, K_5.2
unnamed: D26.2, K_R1.2
unnamed: D27.2, K_F1.2
unnamed: D28.2, K_V1.2
unnamed: D29.2, MX2.2, MX2_1.2
unnamed: D30.2, K_6.2
unnamed: D31.2, K_T1.2
unnamed: D32.2, K_G1.2
unnamed: D33.2, K_B1.2
unnamed: D34.2, K_7.2
unnamed: D35.2, K_Y1.2
unnamed: D36.2, K_H1.2
unnamed: D37.2, K_xn1.2
unnamed: D38.2, K_8.2
unnamed: D39.2, K_U1.2
unnamed: D40.2, K_J1.2
unnamed: D41.2, K_N1.2
unnamed: D42.2, MX3.2
unnamed: D43.2, K_9.2
unnamed: D44.2, K_I1.2
unnamed: D45.2, K_K1.2
unnamed: D46.2, K_M1.2
unnamed: D47.2, K_0.2
unnamed: D48.2, K_O1.2
unnamed: D49.2, K_L1.2
unnamed: D50.2, K_,1.2
unnamed: D51.2, MX4.2
unnamed: D52.2, K_-_1.2
unnamed: D53.2, K_P1.2
unnamed: D54.2, K_;1.2
unnamed: D55.2, K_.1.2
unnamed: D56.2, K_+1.2
unnamed: D57.2, K_{[1.2
unnamed: D58.2, K_'1.2
unnamed: D59.2, K_/?/1.2
unnamed: D60.2, K_BkSp1.2, K_BkSp2.2
unnamed: D61.2, K_]}1.2
unnamed: D62.2, K_RWin1.2, K_RWin2.2
unnamed: D63.2, K_RShift2.2
unnamed: D64.2, K_Delete1.2
unnamed: D65.2, K_|\1.2
unnamed: D66.2, K_Enter1.2
unnamed: D67.2, K_FN1.2
unnamed: D68.2, MX5.2
unnamed: D69.2, D73.4
unnamed: D71.2, D75.4
unnamed: D71.4, D74.2
unnamed: D72.4, D76.2
unnamed: D73.2, D77.4
unnamed: D74.4, D78.2
unnamed: D75.2, D79.4
unnamed: D76.4, D80.2
unnamed: D77.2, D81.4
unnamed: D78.4, D82.2
unnamed: D79.2, D83.4
unnamed: D80.4, D84.2
unnamed: D81.2, D85.4
unnamed: D82.4, D86.2
unnamed: D83.2, D87.4
unnamed: D84.4, D88.2
unnamed: D85.2, D89.4
unnamed: D86.4, D90.2
unnamed: D87.2, D91.4
unnamed: D88.4, D92.2
unnamed: D89.2, D93.4
unnamed: D90.4, D94.2
unnamed: D91.2, D95.4
unnamed: D92.4, D96.2
unnamed: D93.2, D97.4
unnamed: D94.4, D98.2
unnamed: D95.2, D99.4
unnamed: D96.4, D100.2
unnamed: D100.4, D104.2
unnamed: D101.2, D105.4
unnamed: D97.2, D101.4
unnamed: D98.4, D102.2
unnamed: D102.4, D106.2
unnamed: D103.2, D107.4
unnamed: D99.2, D103.4
unnamed: D104.4, D108.2
unnamed: D105.2, D109.4
unnamed: D106.4, D110.2
unnamed: D107.2, D111.4
unnamed: D108.4, D112.2
unnamed: D109.2, D113.4
unnamed: D110.4, D114.2
unnamed: D111.2, D115.4
unnamed: D112.4, D116.2
unnamed: D113.2, D117.4
unnamed: D114.4, D118.2
unnamed: D115.2, D119.4
unnamed: D116.4, D120.2
unnamed: D117.2, D121.4
unnamed: D118.4, D122.2
unnamed: D119.2, D123.4
unnamed: D120.4, D124.2
unnamed: D121.2, D125.4
unnamed: D122.4, D126.2
unnamed: D123.2, D127.4
unnamed: D124.4, D128.2
unnamed: D125.2, D129.4
unnamed: D126.4, D130.2
unnamed: D127.2, D131.4
unnamed: D128.4, D132.2
unnamed: D129.2, D133.4
unnamed: D130.4, D134.2
unnamed: D131.2, D135.4
unnamed: D132.4, D136.2
unnamed: D133.2, D134.4
unnamed: D135.2, D136.4
unnamed: K_4.1, K_C1.1, K_D1.1, K_E1.1, MX1.1, MX1_1.1
unnamed: Q1.1, R69.1
unnamed: R67.2, U2.3, USB1.5, USB1.7
unnamed: R68.2, U2.2, USB1.6, USB1.8
unnamed: R70.2, U1.13, U3.5
unnamed: R71.2, U1.33
unnamed: R73.2, USB1.4
unnamed: R74.2, USB1.10
Row0: D2.1, D5.1, D10.1, D15.1, D20.1, D25.1, D30.1, D34.1, D38.1, D43.1, D47.1, D52.1, D56.1, D60.1, D64.1
Row1: D6.1, D11.1, D16.1, D21.1, D26.1, D31.1, D35.1, D39.1, D44.1, D48.1, D53.1, D57.1, D61.1, D65.1
Row2: D7.1, D12.1, D17.1, D22.1, D27.1, D32.1, D36.1, D40.1, D45.1, D49.1, D54.1, D58.1, D66.1
Row3: D8.1, D13.1, D18.1, D23.1, D28.1, D33.1, D37.1, D41.1, D46.1, D50.1, D55.1, D59.1, D63.1, D67.1
Row4: D9.1, D14.1, D19.1, D24.1, D29.1, D42.1, D51.1, D62.1, D68.1
VCC: F1.2, U2.4, USB1.2, USB1.11
